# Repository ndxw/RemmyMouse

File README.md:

Remmy uses PJRC's USB mouse library found [here](https://www.pjrc.com/teensy/usb_mouse.html), modified to support five mouse buttons.

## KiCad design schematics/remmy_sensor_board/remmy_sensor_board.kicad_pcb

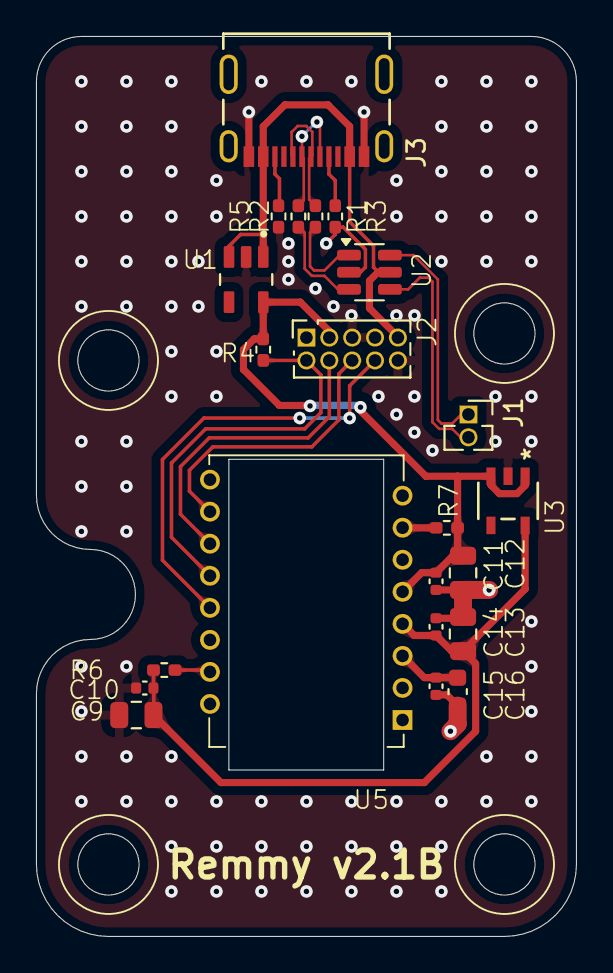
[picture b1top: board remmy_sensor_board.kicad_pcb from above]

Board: 2 copper layers, 30.0 x 50.0 mm, 22 parts (0 on the bottom side), 19 nets.

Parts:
C9, C12, C13: 10u; C_0805_2012Metric
C10, C11, C14, C15: 0.1u; C_0402_1005Metric
C16: 4.7u; C_0603_1608Metric
J1: Conn_01x02; PinSocket_1x02_P1.27mm_Vertical
J2: Conn_02x05_Counter_Clockwise; PinSocket_2x05_P1.27mm_Vertical_CW
J3: USB_C_Receptacle_USB2.0_14P; USB-C_16+8_dummy_SMD
R1, R2: 22; R_0402_1005Metric_Pad0.72x0.64mm_HandSolder
R3, R5: 5.1k; R_0402_1005Metric_Pad0.72x0.64mm_HandSolder
R4, R7: 10k; R_0402_1005Metric_Pad0.72x0.64mm_HandSolder
R6: 39; R_0402_1005Metric_Pad0.72x0.64mm_HandSolder
U1: AP2112K-3.3TRG1; SOT95P280X145-5N
U2: USBLC6-2SC6; SOT-23-6
U3: TPS73219DBVT; DBV5_TEX
U5: PMW3360DM-T2QU

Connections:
+1.9V: C9.2, C10.1, C13.1, C14.1, R6.1, U3.5 (OUT), U5.4 (VDD)
+3.3V: C11.1, C12.1, J2.2, R4.1, R7.1, U1.5 (VOUT), U3.1 (IN), U3.3 (EN), U5.5 (VDDIO)
+5V: J2.5, J3.A4 (VBUS), J3.B4 (VBUS), U1.1 (VIN), U1.3 (EN), U2.5 (VBUS)
GND: C9.1, C10.2, C11.2, C12.2, C13.2, C14.2, C15.2, C16.2, J2.1, J2.3, J2.4, J2.6, J3.A1 (GND), J3.B1 (GND), R3.1, R5.2, U1.2 (GND), U2.2 (GND), U3.2 (GND), U5.8 (GND)
unnamed: J1.1, U2.6 (I/O1)
unnamed: J1.2, U2.4 (I/O2)
unnamed: J2.7, U5.13 (NCS)
unnamed: J2.8, U5.10 (SCLK)
unnamed: J2.9, U5.11 (MOSI)
unnamed: J2.10, R4.2, U5.12 (MISO)
unnamed: J3.A5 (CC1), R3.2
unnamed: J3.B5 (CC2), R5.1
unnamed: J3.A6 (D+), J3.B6 (D+), R1.2
unnamed: J3.A7 (D-), J3.B7 (D-), R2.2
unnamed: R1.1, U2.1 (I/O1)
unnamed: R2.1, U2.3 (I/O2)
unnamed: R6.2, U5.15 (LED_P)
unnamed: R7.2, U5.7 (NRESET)
unnamed: C15.1, C16.1, U5.3 (VDDPIX)

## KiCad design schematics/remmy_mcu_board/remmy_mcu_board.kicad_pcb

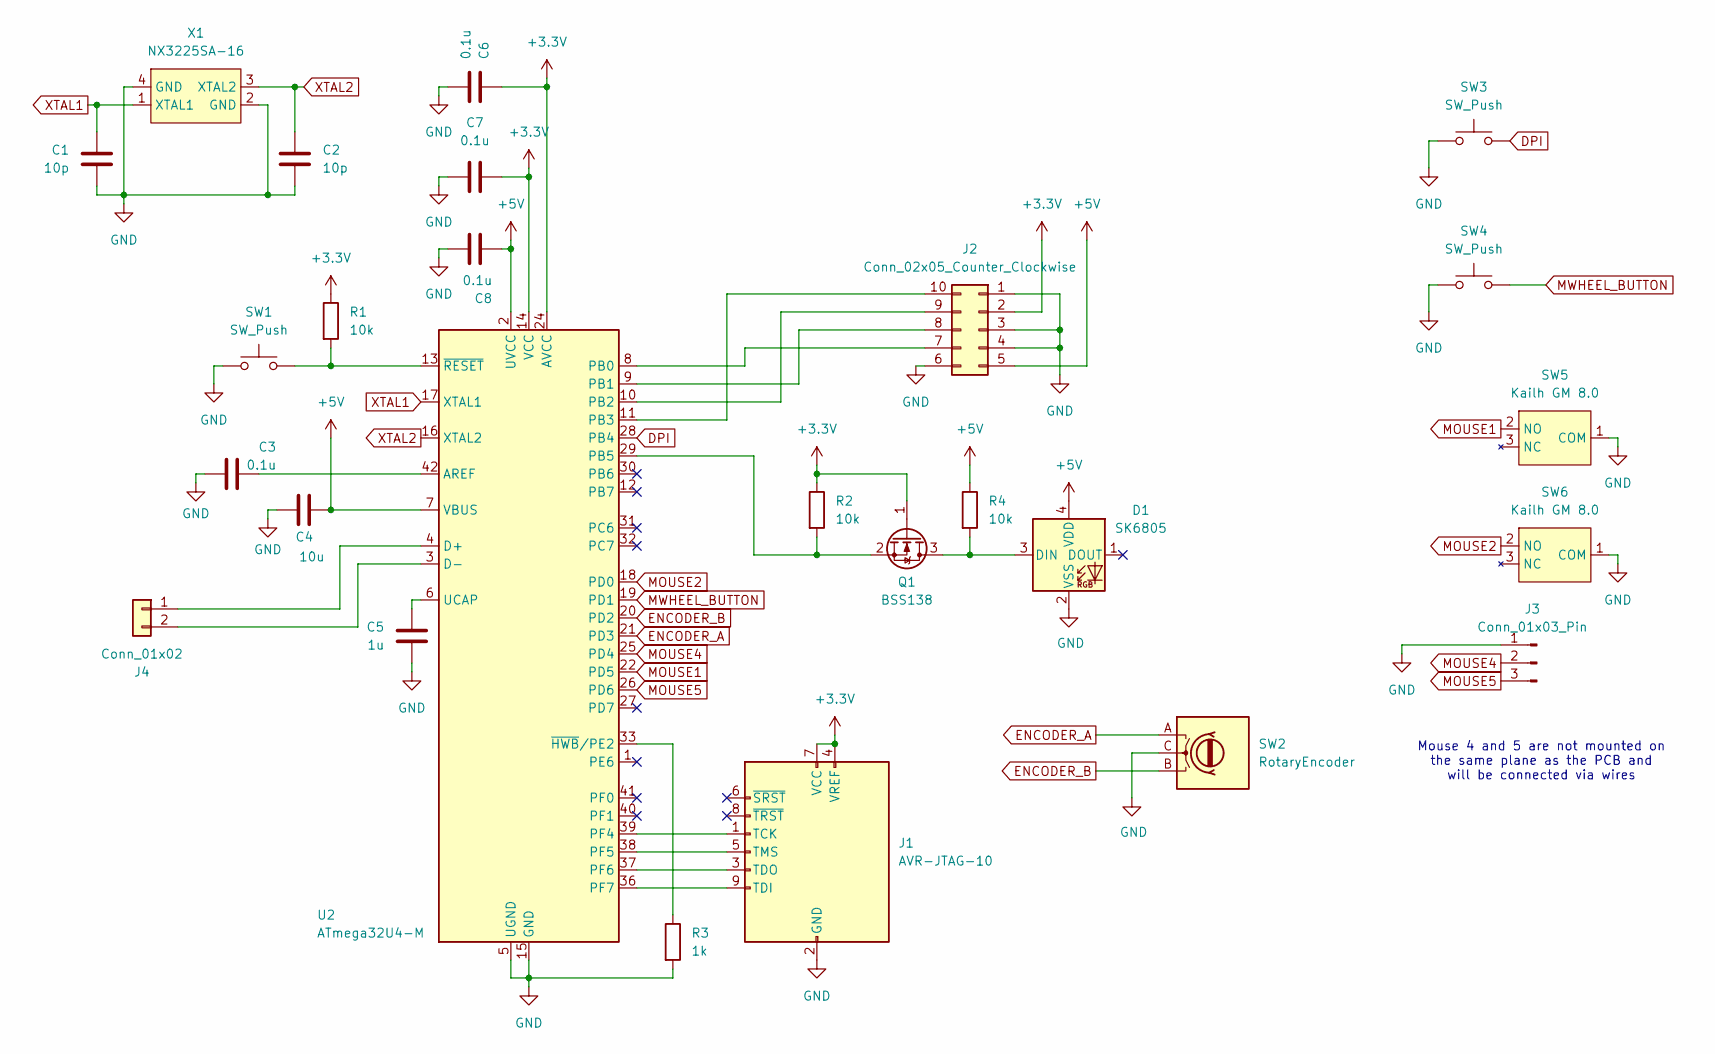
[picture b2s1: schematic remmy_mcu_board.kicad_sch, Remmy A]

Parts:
C1, C2: 10p; C_0201_0603Metric
C3, C6, C7, C8: 0.1u; C_0402_1005Metric
C4: 10u; C_0805_2012Metric
C5: 1u; C_0603_1608Metric
D1: SK6805; LED_SK6805_PLCC4_2.4x2.7mm_P1.3mm
J1: AVR-JTAG-10; PinSocket_2x05_P2.54mm_Vertical
J2: Conn_02x05_Counter_Clockwise; PinSocket_2x05_P1.27mm_Vertical_CW
J3: Conn_01x03_Pin; PinSocket_1x03_P1.27mm_Vertical
J4: Conn_01x02; PinHeader_1x02_P1.27mm_Vertical
Q1: BSS138; SOT-23
R1, R2, R4: 10k; R_0402_1005Metric_Pad0.72x0.64mm_HandSolder
R3: 1k; R_0402_1005Metric_Pad0.72x0.64mm_HandSolder
SW1, SW3: SW_Push; R-667_MIT
SW2: RotaryEncoder; Encoder_TTC_Silver
SW4: SW_Push; SW_PUSH_6mm
SW5, SW6: Kailh GM 8.0; Kailh_GM_8.0
U2: ATmega32U4-M; QFN-44-1EP_7x7mm_P0.5mm_EP5.2x5.2mm_noGNDPlane
X1: NX3225SA-16; CS14520-16M

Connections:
+3.3V: C6.1, C7.1, J1.4 (VREF), J1.7 (VCC), J2.2, Q1.1 (G), R1.1, R2.1, U2.14 (VCC), U2.24 (AVCC), U2.34 (VCC), U2.44 (AVCC)
+5V: C4.1, C8.2, D1.4 (VDD), J2.5, R4.1, U2.2 (UVCC), U2.7 (VBUS)
DPI: SW3.2, U2.28 (PB4)
ENCODER_A: SW2.A, U2.21 (PD3)
ENCODER_B: SW2.B, U2.20 (PD2)
GND: C1.2, C2.2, C3.1, C4.2, C5.2, C6.2, C7.2, C8.1, D1.2 (VSS), J1.2 (GND), J1.10 (GND), J2.1, J2.3, J2.4, J2.6, J3.1, R3.2, SW1.1, SW2.C, SW3.1, SW4.1, SW5.1 (COM), SW6.1 (COM), U2.5 (UGND), U2.15 (GND), U2.23 (GND), U2.35 (GND), U2.43 (GND), U2.45 (GND), X1.2 (GND), X1.4 (GND)
MOUSE1: SW5.2 (NO), U2.22 (PD5)
MOUSE2: SW6.2 (NO), U2.18 (PD0)
MOUSE4: J3.2, U2.25 (PD4)
MOUSE5: J3.3, U2.26 (PD6)
MWHEEL_BUTTON: SW4.2, U2.19 (PD1)
unnamed: D1.3 (DIN), Q1.3 (D), R4.2
unnamed: J1.1 (TCK), U2.39 (PF4)
unnamed: J1.9 (TDI), U2.36 (PF7)
unnamed: J1.3 (TDO), U2.37 (PF6)
unnamed: J1.5 (TMS), U2.38 (PF5)
unnamed: J2.7, U2.8 (PB0)
unnamed: J2.8, U2.9 (PB1)
unnamed: J2.9, U2.10 (PB2)
unnamed: J2.10, U2.11 (PB3)
unnamed: J4.1, U2.4 (D+)
unnamed: J4.2, U2.3 (D-)
unnamed: Q1.2 (S), R2.2, U2.29 (PB5)
unnamed: C3.2, U2.42 (AREF)
unnamed: C5.1, U2.6 (UCAP)
unnamed: R3.1, U2.33 (~HWB/PE2)
unnamed: R1.2, SW1.2, U2.13 (~RESET)
XTAL1: C1.1, U2.17 (XTAL1), X1.1 (XTAL1)
XTAL2: C2.1, U2.16 (XTAL2), X1.3 (XTAL2)

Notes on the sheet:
Mouse 4 and 5 are not mounted on the same plane as the PCB and will be connected via wires

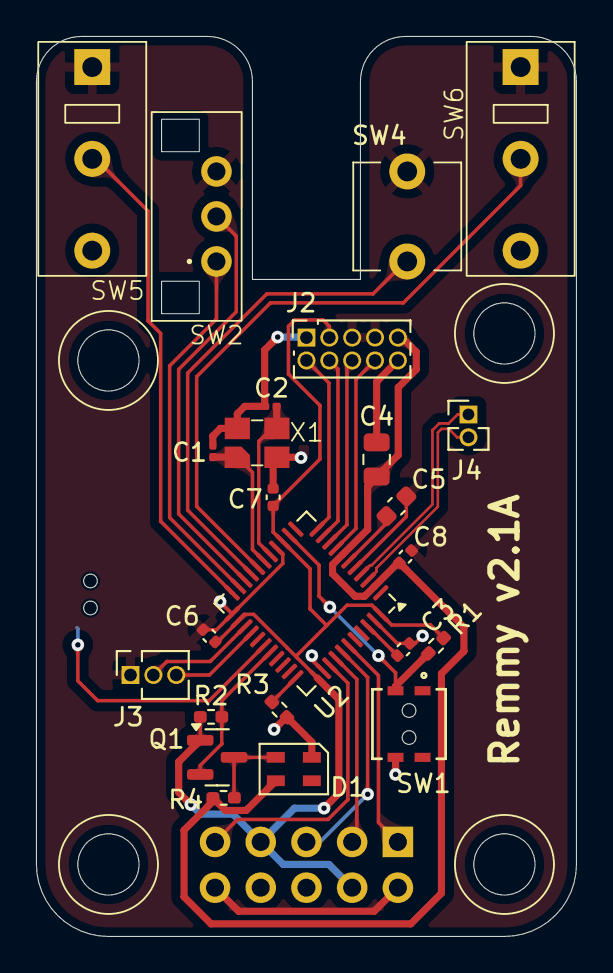
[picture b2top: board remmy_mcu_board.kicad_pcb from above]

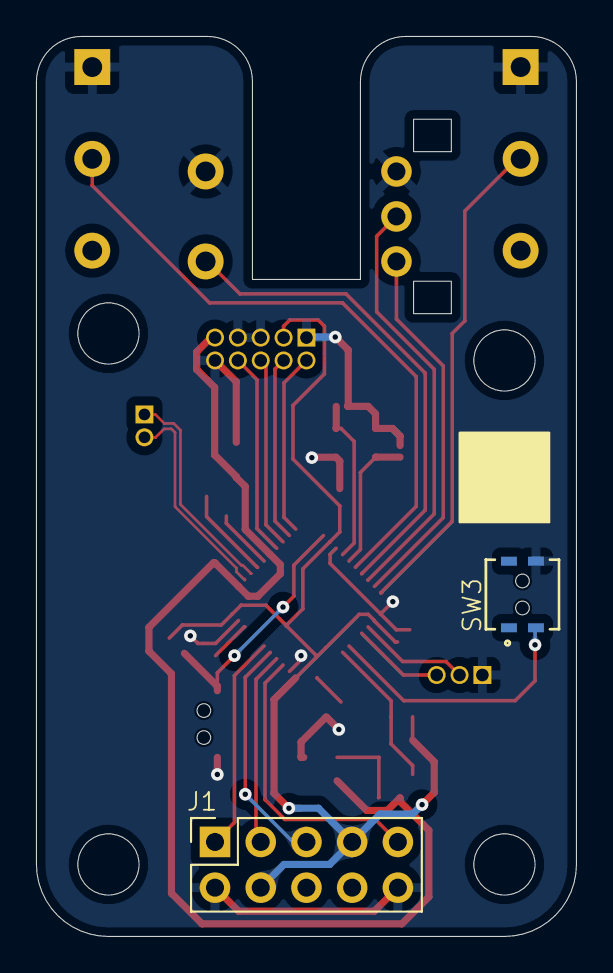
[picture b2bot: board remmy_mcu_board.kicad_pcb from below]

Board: 2 copper layers, 30.0 x 50.0 mm, 26 parts (2 on the bottom side), 29 nets.

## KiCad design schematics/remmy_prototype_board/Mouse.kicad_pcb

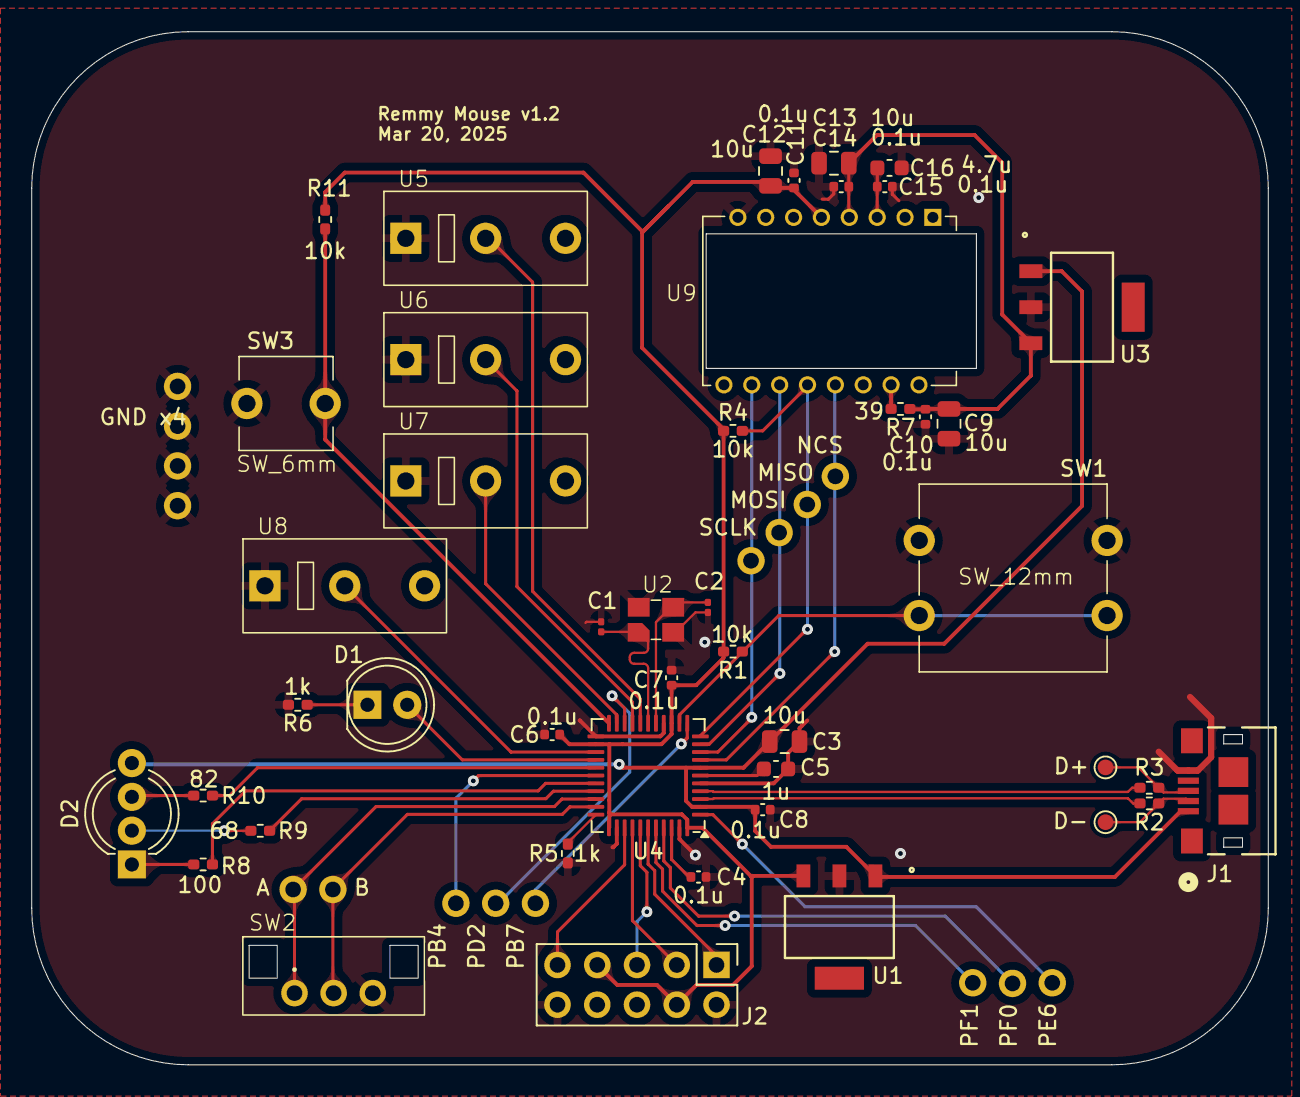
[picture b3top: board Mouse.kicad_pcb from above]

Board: 2 copper layers, 79.0 x 66.0 mm, 61 parts (0 on the bottom side), 45 nets.

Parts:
C1, C2: 10p; C_0201_0603Metric
C3, C9, C12, C13: 10u; C_0805_2012Metric
C4, C6, C7, C8, C10, C11, C14, C15: 0.1u; C_0402_1005Metric
C5: 1u; C_0603_1608Metric
C16: 4.7u; C_0603_1608Metric
D1: LED; LED_D5.0mm
D2: LED_RGBA; LED_D5.0mm-4_RGB_Wide_Pins
J1: USB_B_Micro; CONN_10118193-0001LF_AMP_MicroUSB-B
J2: AVR-JTAG-10; PinSocket_2x05_P2.54mm_Vertical
R1, R4, R11: 10k; R_0402_1005Metric_Pad0.72x0.64mm_HandSolder
R2, R3: 22; R_0402_1005Metric_Pad0.72x0.64mm_HandSolder
R5, R6: 1k; R_0402_1005Metric_Pad0.72x0.64mm_HandSolder
R7: 39; R_0402_1005Metric_Pad0.72x0.64mm_HandSolder
R8: 100; R_0402_1005Metric_Pad0.72x0.64mm_HandSolder
R9: 68; R_0402_1005Metric_Pad0.72x0.64mm_HandSolder
R10: 82; R_0402_1005Metric_Pad0.72x0.64mm_HandSolder
SW1: SW_Push; SW_PUSH_12mm
SW2: RotaryEncoder; Encoder_TTC_Silver
SW3: SW_Push; SW_PUSH_6mm
TP1, TP2: TestPoint; TestPoint_Pad_D1.0mm
TP3, TP4, TP5, TP6, TP7, TP8, TP9, TP10, TP11, TP12, TP13, TP14, TP15, TP16, TP17, TP19: TestPoint; TestPoint_THTPad_D1.75mm_Drill1.0mm
U1, U3: MCP1825S; SOT-223_3MC_MCH
U2: NX3225SA-16; CS14520-16M
U4: ATmega32U4-M; QFN-44-1EP_7x7mm_P0.5mm_EP5.2x5.2mm_noGNDPlane
U5, U6, U7, U8: Kailh GM 8.0; Kailh_GM_8.0
U9: PMW3360DM-T2QU

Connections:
+1.9V: C9.1, C10.1, C13.1, C14.1, R7.1, U3.3 (VO), U9.4 (VDD)
+3.3V: C6.1, C7.1, C11.1, C12.1, J2.4 (VREF), J2.7 (VCC), R1.1, R4.1, R11.1, U1.3 (VO), U4.14 (VCC), U4.24 (AVCC), U4.34 (VCC), U4.44 (AVCC), U9.5 (VDDIO)
+5V: C3.2, C8.2, D2.4 (A), J1.1 (VBUS), U1.1 (VI), U3.1 (VI), U4.2 (UVCC), U4.7 (VBUS)
D+: R2.2, U4.4 (D+)
D-: R3.1, U4.3 (D-)
ENCODER_A: SW2.A, TP7.1, U4.31 (PC6)
ENCODER_B: SW2.B, TP8.1, U4.32 (PC7)
GND: C1.2, C2.2, C3.1, C4.2, C5.2, C6.2, C7.2, C8.1, C9.2, C10.2, C11.2, C12.2, C13.2, C14.2, C15.2, C16.2, J1.5 (GND), J2.2 (GND), J2.10 (GND), R5.2, R6.2, SW1.1, SW2.C, SW3.1, TP9.1, TP16.1, TP17.1, TP19.1, U1.2 (GND), U2.2 (GND), U2.4 (GND), U3.2 (GND), U4.5 (UGND), U4.15 (GND), U4.23 (GND), U4.35 (GND), U4.43 (GND), U5.1 (COM), U6.1 (COM), U7.1 (COM), U8.1 (COM), U9.8 (GND)
LED_RED: D1.2 (A), U4.26 (PD6)
MISO: R4.2, TP6.1, U4.11 (PB3), U9.12 (MISO)
MOSI: TP5.1, U4.10 (PB2), U9.11 (MOSI)
MOUSE1: U4.18 (PD0), U5.2 (NO)
MOUSE2: U4.19 (PD1), U6.2 (NO)
MOUSE4: U4.21 (PD3), U7.2 (NO)
MOUSE5: U4.25 (PD4), U8.2 (NO)
MWHEEL_BUTTON: R11.2, SW3.2, U4.22 (PD5)
NCS: TP3.1, U4.8 (PB0), U9.13 (NCS)
unnamed: D1.1 (K), R6.1
unnamed: D2.3 (BK), R10.2
unnamed: D2.2 (GK), R9.2
unnamed: D2.1 (RK), R8.2
unnamed: J1.3 (D+), R2.1, TP1.1
unnamed: J1.2 (D-), R3.2, TP2.1
unnamed: C4.1, U4.42 (AREF)
unnamed: TP15.1, U4.28 (PB4)
unnamed: TP10.1, U4.12 (PB7)
unnamed: TP11.1, U4.20 (PD2)
unnamed: TP12.1, U4.1 (PE6)
unnamed: TP13.1, U4.41 (PF0)
unnamed: TP14.1, U4.40 (PF1)
unnamed: C5.1, U4.6 (UCAP)
unnamed: R5.1, U4.33 (~HWB/PE2)
unnamed: R7.2, U9.15 (LED_P)
unnamed: C15.1, C16.1, U9.3 (VDDPIX)
RGBA_BLUE: R10.1, U4.27 (PD7)
RGBA_GREEN: R9.1, U4.30 (PB6)
RGBA_RED: R8.1, U4.29 (PB5)
SCLK: TP4.1, U4.9 (PB1), U9.10 (SCLK)
TCK: J2.1 (TCK), U4.39 (PF4)
TDI: J2.9 (TDI), U4.36 (PF7)
TDO: J2.3 (TDO), U4.37 (PF6)
TMS: J2.5 (TMS), U4.38 (PF5)
XTAL1: C1.1, U2.1 (XTAL1), U4.17 (XTAL1)
XTAL2: C2.1, U2.3 (XTAL2), U4.16 (XTAL2)
nRESET: R1.2, SW1.2, U4.13 (~RESET)

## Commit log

2025-02-25 init commit
2025-05-15 v2.0 pcb complete, dpi yet to be implemented
2025-05-15 rm datasheets
2025-05-16 fixed wheel direction and swapped mouse4/5
2025-05-18 completed dpi button
2025-05-18 rm circle.h
2025-05-18 added images
2025-05-18 rm sample firmware
2025-06-12 broken spi comm
2025-06-22 updated shell model
